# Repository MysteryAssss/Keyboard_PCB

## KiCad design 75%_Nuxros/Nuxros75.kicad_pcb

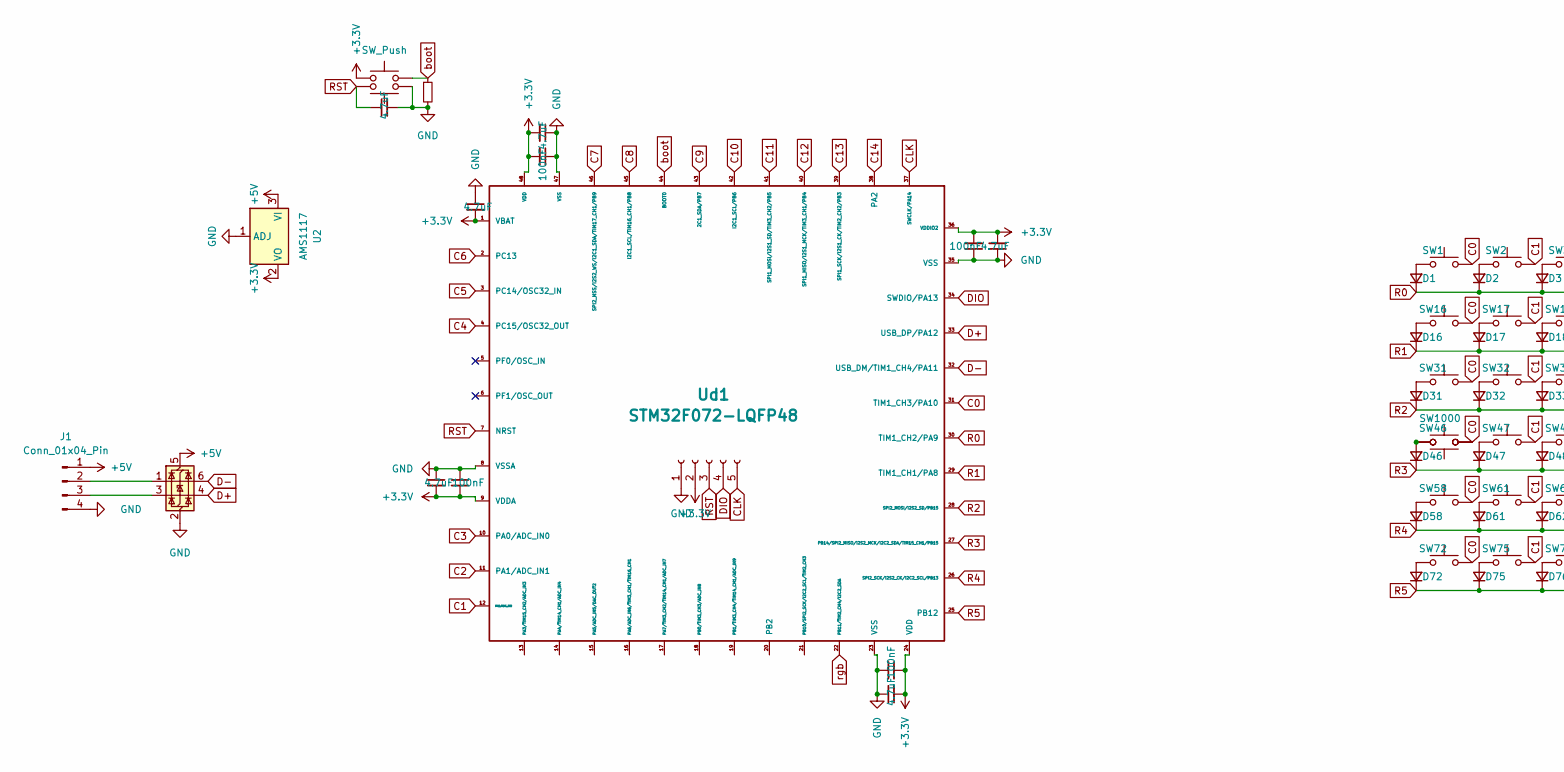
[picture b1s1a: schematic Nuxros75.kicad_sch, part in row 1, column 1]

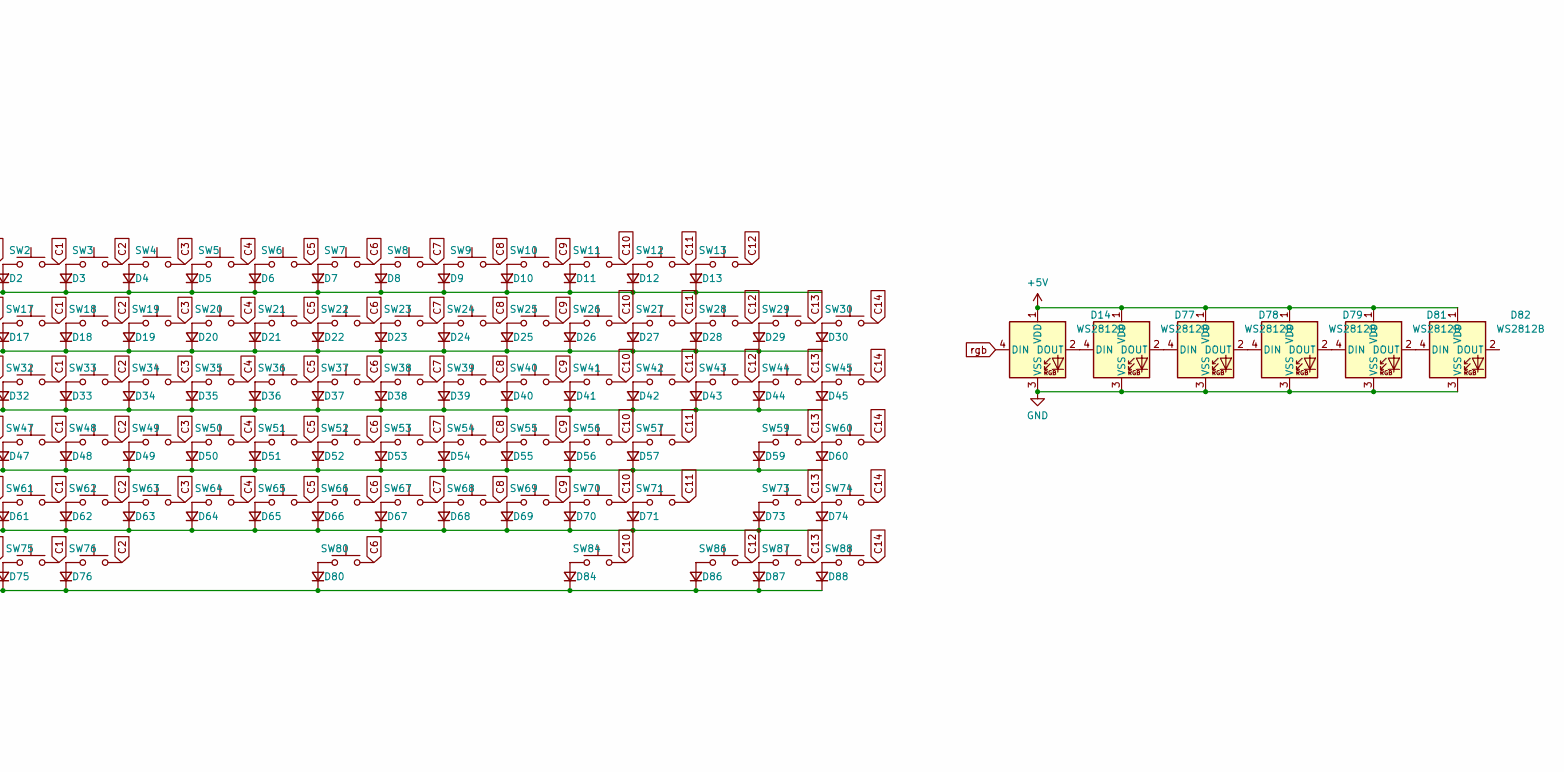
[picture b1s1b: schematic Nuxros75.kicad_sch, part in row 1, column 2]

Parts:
C1, C3, C5, C7: 100nF; C_0805_2012Metric
C2, C4, C6, C8, C9, C10: 4.7uF; C_0805_2012Metric
D1, D2, D3, D4, D5, D6, D7, D8, D9, D10, D11, D12, D13, D16, D17, D18, D19, D20, D21, D22, D23, D24, D25, D26, D27, D28, D29, D30, D31, D32, D33, D34, D35, D36, D37, D38, D39, D40, D41, D42, D43, D44, D45, D46, D47, D48, D49, D50, D51, D52, D53, D54, D55, D56, D57, D58, D59, D60, D61, D62, D63, D64, D65, D66, D67, D68, D69, D70, D71, D72, D73, D74, D75, D76, D80, D84, D86, D87, D88: D_Small; D_SOD-123
D14, D77, D78, D79, D81, D82: WS2812B; LED_WS2812B_PLCC4_5.0x5.0mm_P3.2mm
J1: Conn_01x04_Pin; JST_SH_SM04B-SRSS-TB_1x04-1MP_P1.00mm_Horizontal
J2: Conn_01x05_Socket; JST_PH_B5B-PH-K_1x05_P2.00mm_Vertical
R1: R_Small; R_0805_2012Metric
SW1, SW2, SW3, SW4, SW5, SW6, SW7, SW8, SW9, SW10, SW11, SW12, SW13, SW16, SW17, SW18, SW19, SW20, SW21, SW22, SW23, SW24, SW25, SW26, SW27, SW28, SW30, SW32, SW33, SW34, SW35, SW36, SW37, SW38, SW39, SW40, SW41, SW42, SW43, SW45, SW47, SW48, SW49, SW50, SW51, SW52, SW53, SW54, SW55, SW56, SW57, SW60, SW61, SW62, SW63, SW64, SW65, SW66, SW67, SW68, SW69, SW70, SW73, SW74, SW75, SW86, SW87, SW88: SW_Push; MXOnly-1U_N
SW29: SW_Push; MXOnly-2U_N
SW31, SW44, SW72, SW76, SW84: SW_Push; MXOnly-1.5U_N
SW46, SW71: SW_Push; MXOnly-1.75U_N
SW58, SW59: SW_Push; MXOnly-2.25U_N
SW80: SW_Push; MXOnly-7U-ReversedStabilizers_N
SW1000: SW_Push; MXOnly-1.25U_N
SWbôt1: SW_Push; JST_EH_B2B-EH-A_1x02_P2.50mm_Vertical
SWbôtrst1: SW_Push; JST_EH_B2B-EH-A_1x02_P2.50mm_Vertical
U2: AMS1117; SOT-223-3_TabPin2
U3: USBLC6-2SC6; SOT-23-6
Ud1: STM32F072-LQFP48; LQFP-48_7x7mm_P0.5mm

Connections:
+3.3V: C1.2, C2.2, C3.2, C4.2, C5.2, C6.2, C7.2, C8.2, C9.2, J2.2, SWbôt1.1, U2.2 (VO), Ud1.1 (VBAT), Ud1.9 (VDDA), Ud1.24 (VDD), Ud1.36 (VDDIO2), Ud1.48 (VDD)
+5V: D14.1 (VDD), D77.1 (VDD), D78.1 (VDD), D79.1 (VDD), D81.1 (VDD), D82.1 (VDD), J1.1, U2.3 (VI), U3.5 (VBUS)
C0: SW1.2, SW16.2, SW31.2, SW46.2, SW58.2, SW72.2, SW1000.1, Ud1.31 (TIM1_CH3/PA10)
C1: SW2.2, SW17.2, SW32.2, SW47.2, SW61.2, SW75.2, Ud1.12 (PA2/ADC_IN2)
C2: SW3.2, SW18.2, SW33.2, SW48.2, SW62.2, SW76.2, Ud1.11 (PA1/ADC_IN1)
C3: SW4.2, SW19.2, SW34.2, SW49.2, SW63.2, Ud1.10 (PA0/ADC_IN0)
C4: SW5.2, SW20.2, SW35.2, SW50.2, SW64.2, Ud1.4 (PC15/OSC32_OUT)
C5: SW6.2, SW21.2, SW36.2, SW51.2, SW65.2, Ud1.3 (PC14/OSC32_IN)
C6: SW7.2, SW22.2, SW37.2, SW52.2, SW66.2, SW80.2, Ud1.2 (PC13)
C7: SW8.2, SW23.2, SW38.2, SW53.2, SW67.2, Ud1.46 (SPI2_NSS/I2S2_WS/I2C1_SDA/TIM17_CH1/PB9)
C8: SW9.2, SW24.2, SW39.2, SW54.2, SW68.2, Ud1.45 (I2C1_SCL/TIM16_CH1/PB8)
C9: SW10.2, SW25.2, SW40.2, SW55.2, SW69.2, Ud1.43 (2C1_SDA/PB7)
C10: SW11.2, SW26.2, SW41.2, SW56.2, SW70.2, SW84.2, Ud1.42 (I2C1_SCL/PB6)
C11: SW12.2, SW27.2, SW42.2, SW57.2, SW71.2, Ud1.41 (SPI1_MOSI/I2S1_SD/TIM3_CH2/PB5)
C12: SW13.2, SW28.2, SW43.2, SW86.2, Ud1.40 (SPI1_MISO/I2S1_MCK/TIM3_CH1/PB4)
C13: SW29.2, SW44.2, SW59.2, SW73.2, SW87.2, Ud1.39 (SPI1_SCK/I2S1_CK/TIM2_CH2/PB3)
C14: SW30.2, SW45.2, SW60.2, SW74.2, SW88.2, Ud1.38 (PA2)
CLK: J2.5, Ud1.37 (SWCLK/PA14)
D+: U3.4 (I/O2), Ud1.33 (USB_DP/PA12)
D-: U3.6 (I/O1), Ud1.32 (USB_DM/TIM1_CH4/PA11)
DIO: J2.4, Ud1.34 (SWDIO/PA13)
GND: C1.1, C2.1, C3.1, C4.1, C5.1, C6.1, C7.1, C8.1, C9.1, C10.2, D14.3 (VSS), D77.3 (VSS), D78.3 (VSS), D79.3 (VSS), D81.3 (VSS), D82.3 (VSS), J1.4, J2.1, R1.2, SWbôtrst1.1, U2.1 (ADJ), U3.2 (GND), Ud1.8 (VSSA), Ud1.23 (VSS), Ud1.35 (VSS), Ud1.47 (VSS)
unnamed: D1.2 (A), SW1.1
unnamed: D2.2 (A), SW2.1
unnamed: D3.2 (A), SW3.1
unnamed: D4.2 (A), SW4.1
unnamed: D5.2 (A), SW5.1
unnamed: D6.2 (A), SW6.1
unnamed: D7.2 (A), SW7.1
unnamed: D8.2 (A), SW8.1
unnamed: D9.2 (A), SW9.1
unnamed: D10.2 (A), SW10.1
unnamed: D11.2 (A), SW11.1
unnamed: D12.2 (A), SW12.1
unnamed: D13.2 (A), SW13.1
unnamed: D14.2 (DOUT), D77.4 (DIN)
unnamed: D16.2 (A), SW16.1
unnamed: D17.2 (A), SW17.1
unnamed: D18.2 (A), SW18.1
unnamed: D19.2 (A), SW19.1
unnamed: D20.2 (A), SW20.1
unnamed: D21.2 (A), SW21.1
unnamed: D22.2 (A), SW22.1
unnamed: D23.2 (A), SW23.1
unnamed: D24.2 (A), SW24.1
unnamed: D25.2 (A), SW25.1
unnamed: D26.2 (A), SW26.1
unnamed: D27.2 (A), SW27.1
unnamed: D28.2 (A), SW28.1
unnamed: D29.2 (A), SW29.1
unnamed: D30.2 (A), SW30.1
unnamed: D31.2 (A), SW31.1
unnamed: D32.2 (A), SW32.1
unnamed: D33.2 (A), SW33.1
unnamed: D34.2 (A), SW34.1
unnamed: D35.2 (A), SW35.1
unnamed: D36.2 (A), SW36.1
unnamed: D37.2 (A), SW37.1
unnamed: D38.2 (A), SW38.1
unnamed: D39.2 (A), SW39.1
unnamed: D40.2 (A), SW40.1
unnamed: D41.2 (A), SW41.1
unnamed: D42.2 (A), SW42.1
unnamed: D43.2 (A), SW43.1
unnamed: D44.2 (A), SW44.1
unnamed: D45.2 (A), SW45.1
unnamed: D46.2 (A), SW46.1, SW1000.2
unnamed: D47.2 (A), SW47.1
unnamed: D48.2 (A), SW48.1
unnamed: D49.2 (A), SW49.1
unnamed: D50.2 (A), SW50.1
unnamed: D51.2 (A), SW51.1
unnamed: D52.2 (A), SW52.1
unnamed: D53.2 (A), SW53.1
unnamed: D54.2 (A), SW54.1
unnamed: D55.2 (A), SW55.1
unnamed: D56.2 (A), SW56.1
unnamed: D57.2 (A), SW57.1
unnamed: D58.2 (A), SW58.1
unnamed: D59.2 (A), SW59.1
unnamed: D60.2 (A), SW60.1
unnamed: D61.2 (A), SW61.1
unnamed: D62.2 (A), SW62.1
unnamed: D63.2 (A), SW63.1
unnamed: D64.2 (A), SW64.1
unnamed: D65.2 (A), SW65.1
unnamed: D66.2 (A), SW66.1
unnamed: D67.2 (A), SW67.1
unnamed: D68.2 (A), SW68.1
unnamed: D69.2 (A), SW69.1
unnamed: D70.2 (A), SW70.1
unnamed: D71.2 (A), SW71.1
unnamed: D72.2 (A), SW72.1
unnamed: D73.2 (A), SW73.1
unnamed: D74.2 (A), SW74.1
unnamed: D75.2 (A), SW75.1
unnamed: D76.2 (A), SW76.1
unnamed: D77.2 (DOUT), D78.4 (DIN)
unnamed: D78.2 (DOUT), D79.4 (DIN)
unnamed: D79.2 (DOUT), D81.4 (DIN)
unnamed: D80.2 (A), SW80.1
unnamed: D81.2 (DOUT), D82.4 (DIN)
unnamed: D84.2 (A), SW84.1
unnamed: D86.2 (A), SW86.1
unnamed: D87.2 (A), SW87.1
unnamed: D88.2 (A), SW88.1
unnamed: J1.2, U3.1 (I/O1)
unnamed: J1.3, U3.3 (I/O2)
R0: D1.1 (K), D2.1 (K), D3.1 (K), D4.1 (K), D5.1 (K), D6.1 (K), D7.1 (K), D8.1 (K), D9.1 (K), D10.1 (K), D11.1 (K), D12.1 (K), D13.1 (K), Ud1.30 (TIM1_CH2/PA9)
R1: D16.1 (K), D17.1 (K), D18.1 (K), D19.1 (K), D20.1 (K), D21.1 (K), D22.1 (K), D23.1 (K), D24.1 (K), D25.1 (K), D26.1 (K), D27.1 (K), D28.1 (K), D29.1 (K), D30.1 (K), Ud1.29 (TIM1_CH1/PA8)
R2: D31.1 (K), D32.1 (K), D33.1 (K), D34.1 (K), D35.1 (K), D36.1 (K), D37.1 (K), D38.1 (K), D39.1 (K), D40.1 (K), D41.1 (K), D42.1 (K), D43.1 (K), D44.1 (K), D45.1 (K), Ud1.28 (SPI2_MOSI/I2S2_SD/PB15)
R3: D46.1 (K), D47.1 (K), D48.1 (K), D49.1 (K), D50.1 (K), D51.1 (K), D52.1 (K), D53.1 (K), D54.1 (K), D55.1 (K), D56.1 (K), D57.1 (K), D59.1 (K), D60.1 (K), Ud1.27 (PB14/SPI2_MISO/I2S2_MCK/I2C2_SDA/TIM15_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)
R4: D58.1 (K), D61.1 (K), D62.1 (K), D63.1 (K), D64.1 (K), D65.1 (K), D66.1 (K), D67.1 (K), D68.1 (K), D69.1 (K), D70.1 (K), D71.1 (K), D73.1 (K), D74.1 (K), Ud1.26 (SPI2_SCK/I2S2_CK/I2C2_SCL/PB13)
R5: D72.1 (K), D75.1 (K), D76.1 (K), D80.1 (K), D84.1 (K), D86.1 (K), D87.1 (K), D88.1 (K), Ud1.25 (PB12)
RST: C10.1, J2.3, SWbôtrst1.2, Ud1.7 (NRST)
boot: R1.1, SWbôt1.2, Ud1.44 (BOOT0)
rgb: D14.4 (DIN), Ud1.22 (PB11/TIM2_CH4/I2C2_SDA)

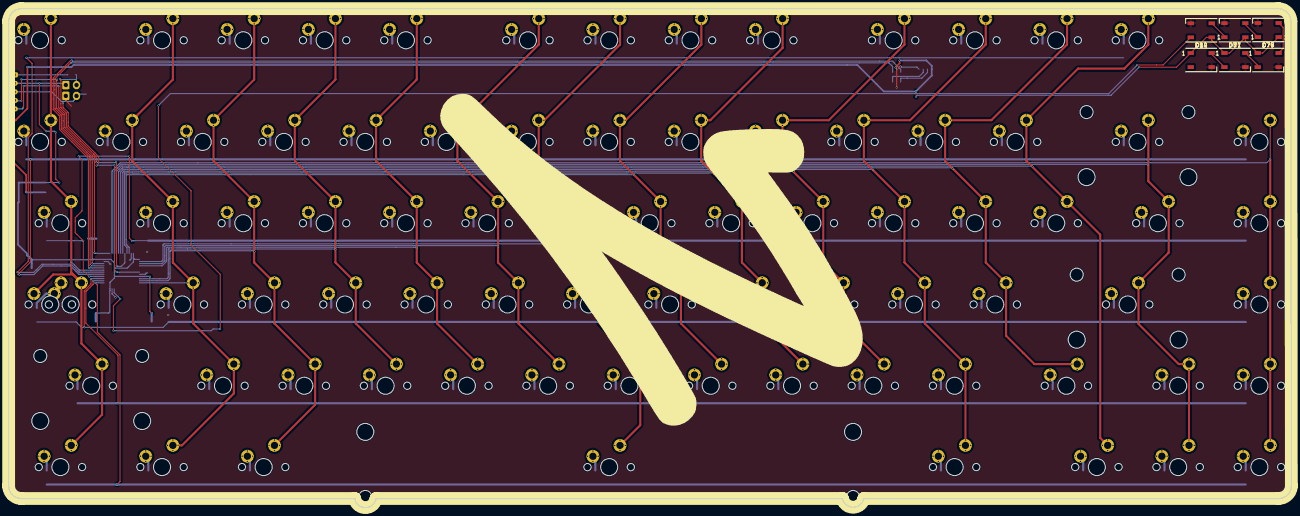
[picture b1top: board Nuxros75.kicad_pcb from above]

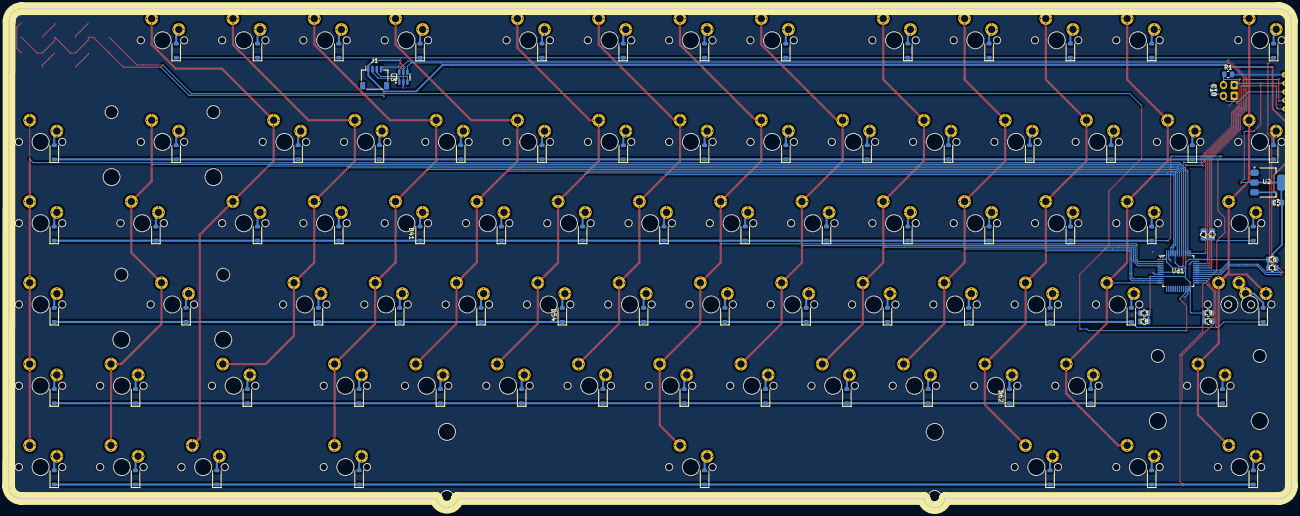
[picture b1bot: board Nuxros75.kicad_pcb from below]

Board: 2 copper layers, 300.6 x 116.9 mm, 183 parts (94 on the bottom side), 117 nets.
